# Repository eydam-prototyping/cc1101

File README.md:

# CC1101 Driver for Raspberry Pi and Micropython

This project provides a Python driver for the CC1101 transceiver chip, enabling seamless integration with Raspberry Pi and other compatible platforms. The driver supports data transmission and reception, making it ideal for wireless communication projects.

## Wiring

Connect two devices, if you want to run all samples. Otherwise you only need one.

| CC1101 (1) | CC1101 (2) | Raspberry Pi | Meaning      |
|------------|------------|--------------|--------------|
| VDD        | VDD        | 3.3V (17)    | Power Supply |
| GND        | GND        | GND (23)     | Ground       |
| MOSI       | MOSI       | GPIO10 (19)  | SPI MOSI     |
| MISO       | MISO       | GPIO9 (21)   | SPI MISO     |
| SCK        | SCK        | GPIO11 (23)  | SPI SCLK     |
| CSN        | -          | GPIO8 (24)   | SPI CE0      |
| -          | CSN        | GPIO7 (26)   | SPI CE1      |
| GDO0       | -          | GPIO23 (16)  | RX/TX Done   |
| -          | GDO0       | GPIO24 (18)  | RX/TX Done   |
| GDO2       | -          | GPIO17 (11)  | -            |
| -          | GDO2       | GPIO18 (12)  | -            |

## Usage
* Connect the CC1101 module to your hardware as per your wiring setup.

* Run an example script:

    * For transmission:
        ```bash
        python examples/transmitter.py
        ```
    * For reception:
        ```bash
        python examples/receiver.py
        ```

## Project Structure
* **src/:** Contains the main driver code.
* **examples/**: Example scripts for transmission and reception.
* **tests/**: Unit tests for the driver.

## Meaning of Parameters

### Base Frequency

```python
cc1101.configurator.set_base_frequency_hz(433.92e6)
cc1101.set_configuration()
```
The base frequency is a key parameter in configuring the CC1101 transceiver, as it defines the central frequency at which the device operates. This parameter determines the starting point of the RF (radio frequency) signal generation and reception, which is crucial for ensuring compatibility with the chosen communication standard or regulatory requirements.

The base frequency is typically set in the range of 300 MHz to 928 MHz, depending on the hardware and regional regulations. For example, in the ISM (Industrial, Scientific, and Medical) bands, common frequencies include 433 MHz, 868 MHz, and 915 MHz.

*Note: Make sure, you have the right Antenna connected*

### Modulation Format

```python
# 0: 2-FSK
# 1: GFSK
# 3: ASK_OOK
# 4: 4-FSK
# 7: MSK
cc1101.configurator.set_modulation_format(0)
cc1101.set_configuration()
```
The modulation format determines how data is encoded onto the carrier frequency for transmission and decoded during reception. This parameter is essential for ensuring compatibility between transmitting and receiving devices, as both must use the same modulation scheme to communicate effectively.

The CC1101 supports several modulation formats, including:
  * 2/4-FSK (Frequency Shift Keying): A robust modulation scheme commonly used in environments with high interference.
  * GFSK (Gaussian Frequency Shift Keying): A variation of FSK with smoother transitions, reducing spectral bandwidth and interference.
  * ASK/OOK (Amplitude Shift Keying/On-Off Keying): Simple schemes often used in low-power, short-range applications like remote controls.
  * MSK (Minimum Shift Keying): Provides high spectral efficiency, ideal for data-intensive applications.

The choice of modulation format impacts key aspects of the communication, including data rate, power consumption, and signal robustness. For example, FSK is highly reliable in noisy environments, while OOK is energy-efficient but more susceptible to interference.

#### 2-FSK (2 Frequency Shift Keying)

2-FSK is a digital modulation scheme where the carrier frequency shifts between two discrete frequencies to represent binary data (0 and 1). It is one of the simplest forms of frequency modulation and is widely used for robust communication in environments with noise or interference.

**Relevant CC1101 Parameters:**

  * Deviation: The difference between the carrier frequency and the modulated frequencies.

#### 4-FSK (4 Frequency Shift Keying)

Like 2-FSK, but with 4 Frequencies.

#### ASK (Amplitude Shift Keying) / OOK (On-Off Keying)

ASK (Amplitude Shift Keying) is a modulation scheme where the amplitude of the carrier signal varies to represent binary data. Unlike OOK, which is a subset of ASK with only two states (presence or absence of a signal), ASK can include more amplitude levels for more complex data encoding, though in most applications, it uses only two states:

High Amplitude represents binary 1.
Low Amplitude (or Zero in OOK) represents binary 0.
ASK/OOK is commonly used in simple, low-power communication systems such as wireless sensors, keyless entry systems, and remote controls.

**Relevant CC1101 Parameters:**

  * PA-Table Setting: \
      Byte 0 represents the power for a logical zero\
      Byte 1 represents the power for a logical one

  * FREND0.PA_POWER represents the PA power setting, that is used for a logical one. Default is 1.

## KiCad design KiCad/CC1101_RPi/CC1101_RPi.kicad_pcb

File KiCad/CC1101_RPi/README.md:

# PCB CC1101_RPi

## Wiring

| CH1, 433 MHz | CH2, 433 MHz | CH3, 868 MHz | CH4, 868 MHz | Raspberry Pi | Meaning      |
|--------------|--------------|--------------|--------------|--------------|--------------|
| VDD          | VDD          | -            | -            | 3.3V         | Power Supply |
| GND          | GND          | -            | -            | GND          | Ground       |
|              |              |              |              |              |              |
| MOSI         | MOSI         | -            | -            | GPIO10       | SPI0 MOSI    |
| MISO         | MISO         | -            | -            | GPIO9        | SPI0 MISO    |
| SCK          | SCK          | -            | -            | GPIO11       | SPI0 SCLK    |
|              |              |              |              |              |              |
| CSN          | -            | -            | -            | GPIO8        | SPI0 CE0     |
| GDO0         | -            | -            | -            | GPIO5        | -            |
| GDO2         | -            | -            | -            | GPIO6        | -            |
|              |              |              |              |              |              |
| -            | CSN          | -            | -            | GPIO7        | SPI0 CE1     |
| -            | GDO0         | -            | -            | GPIO22       | -            |
| -            | GDO2         | -            | -            | GPIO23       | -            |
|              |              |              |              |              |              |
| -            | -            | MOSI         | MOSI         | GPIO20       | SPI1 MOSI    |
| -            | -            | MISO         | MISO         | GPIO19       | SPI1 MISO    |
| -            | -            | SCK          | SCK          | GPIO21       | SPI1 SCLK    |
|              |              |              |              |              |              |
| -            | -            | CSN          | -            | GPIO18       | SPI1 CE0     |
| -            | -            | GDO0         | -            | GPIO24       | -            |
| -            | -            | GDO2         | -            | GPIO25       | -            |
|              |              |              |              |              |              |
| -            | -            | -            | CSN          | GPIO17       | SPI1 CE1     |
| -            | -            | -            | GDO0         | GPIO26       | -            |
| -            | -            | -            | GDO2         | GPIO27       | -            |

# Setup

Enable I2C and SPI in `/boot/firmware/config.txt`:

```
dtparam=i2c_arm=on
dtparam=spi=on
dtoverlay=spi1-2cs
```

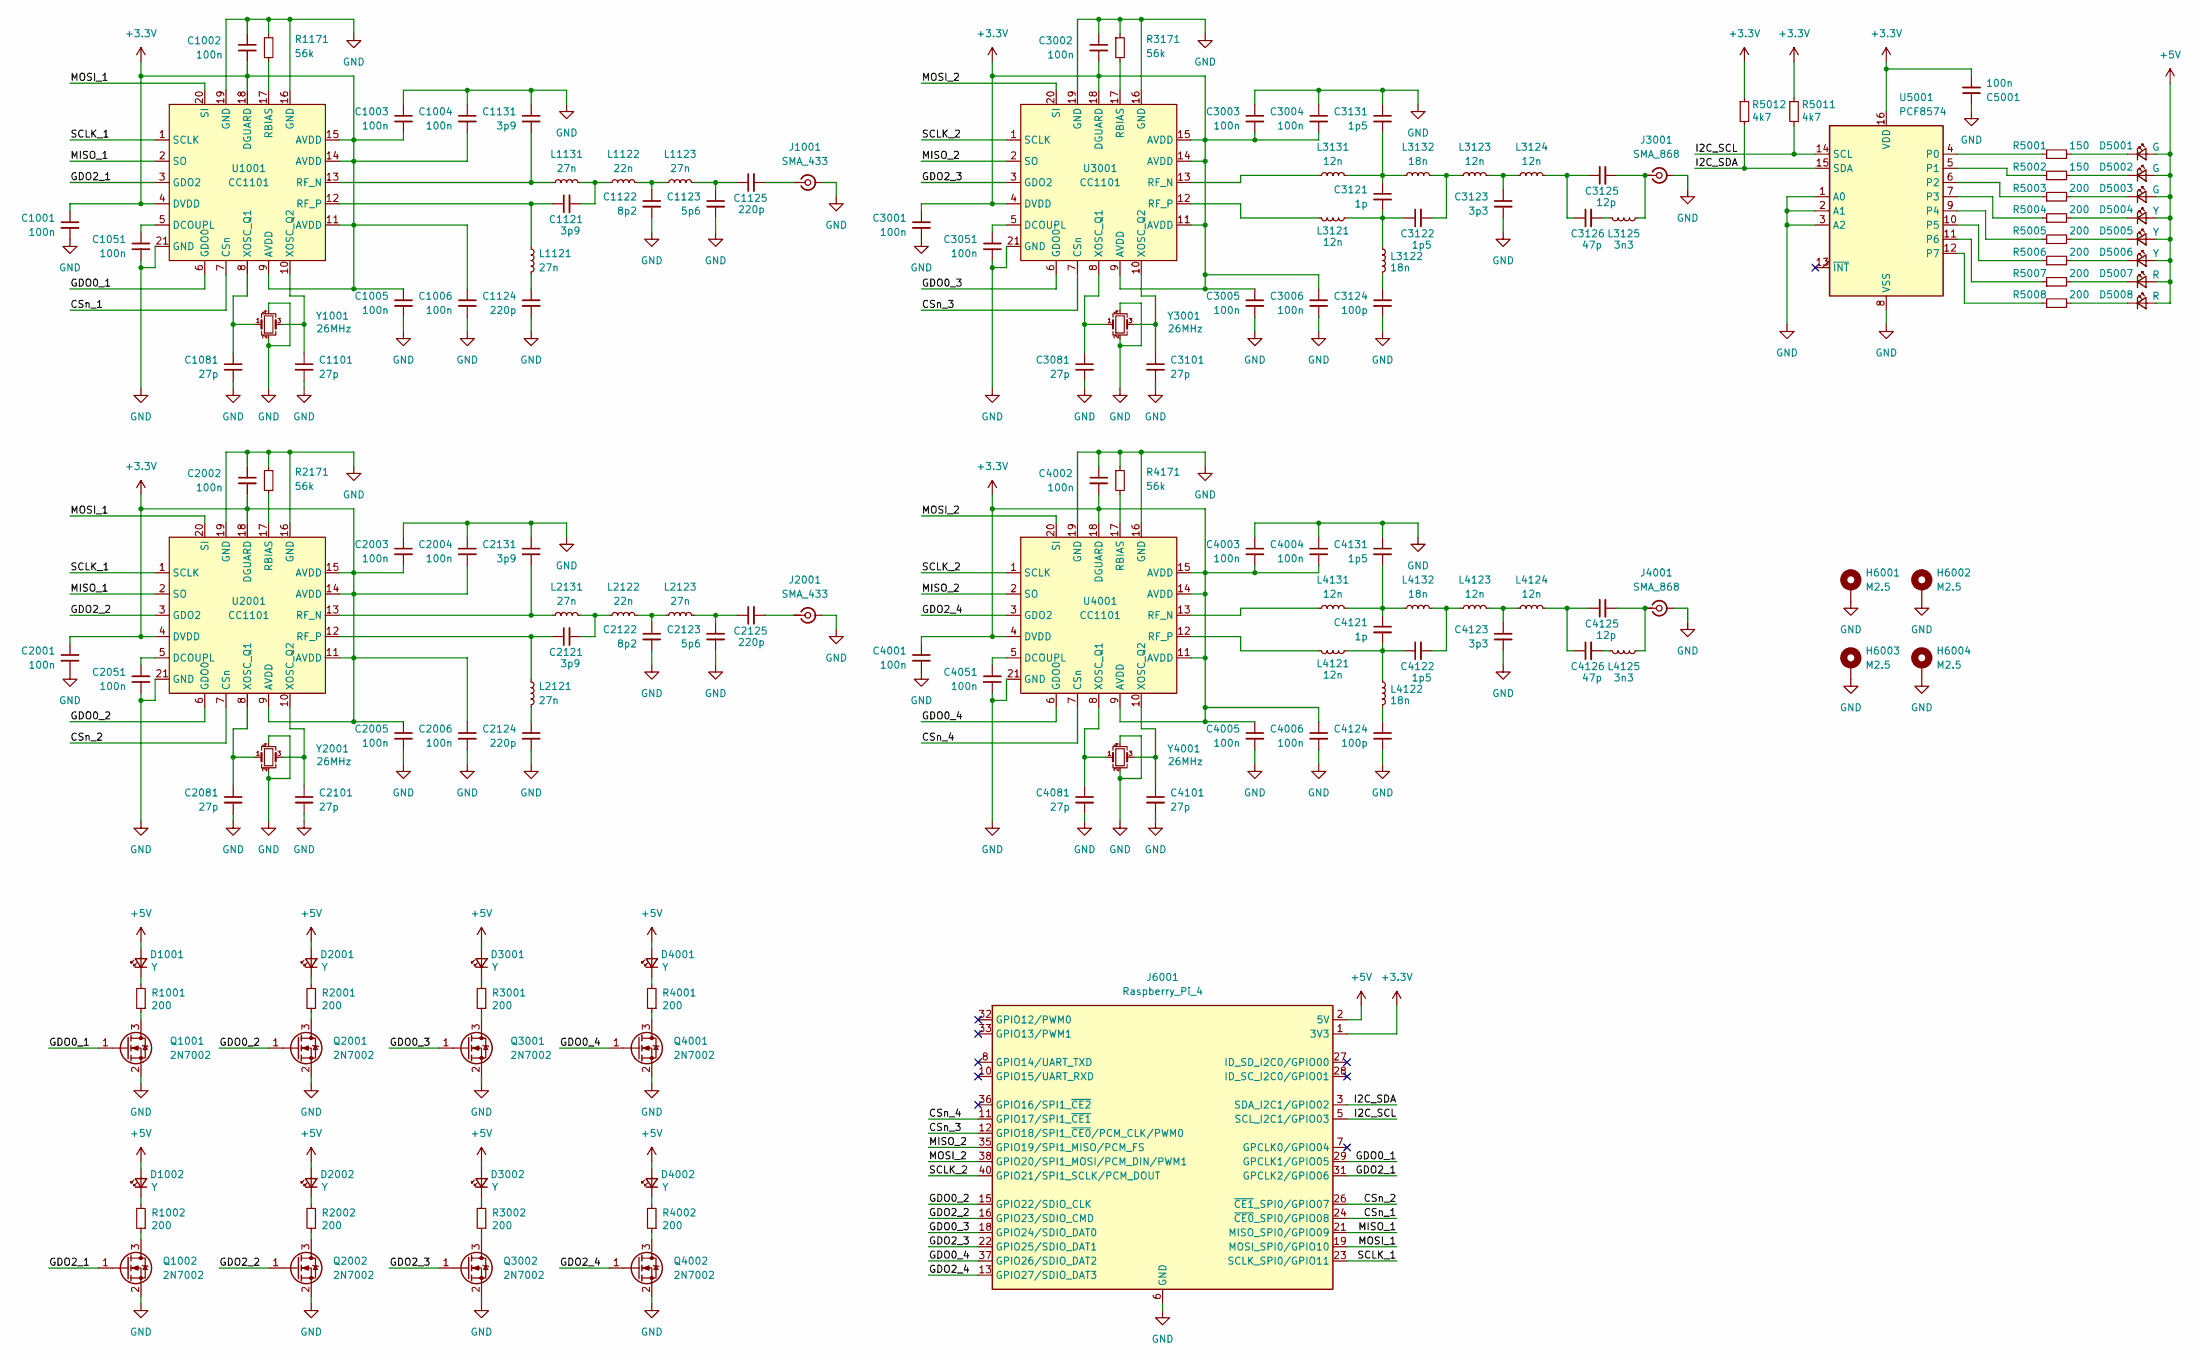
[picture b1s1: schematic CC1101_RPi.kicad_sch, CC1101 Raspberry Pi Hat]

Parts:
C1001, C1002, C1003, C1004, C1005, C1006, C1051, C2001, C2002, C2003, C2004, C2005, C2006, C2051, C3001, C3002, C3003, C3004, C3005, C3006, C3051, C4001, C4002, C4003, C4004, C4005, C4006, C4051, C5001: 100n; C_0402_1005Metric; MFRPartNo CL05B104KB54PNC; LCSC C307331
C1081, C1101, C2081, C2101, C3081, C3101, C4081, C4101: 27p; C_0402_1005Metric; MFRPartNo GRM1555C1H270FA01D; LCSC C161544
C1121, C1131, C2121, C2131: 3p9; C_0402_1005Metric; MFRPartNo GRM1555C1H3R9CA01D; LCSC C85940
C1122, C2122: 8p2; C_0402_1005Metric; MFRPartNo GRM1555C1H8R2CA01D; LCSC C76984
C1123, C2123: 5p6; C_0402_1005Metric; MFRPartNo GRM1555C1H5R6BA01D; LCSC C76976
C1124, C1125, C2124, C2125: 220p; C_0402_1005Metric; MFRPartNo GRM1555C1H221JA01D; LCSC C71693
C3121, C4121: 1p; C_0402_1005Metric; MFRPartNo GRM1555C1H1R0CA01D; LCSC C76953
C3122, C3131, C4122, C4131: 1p5; C_0402_1005Metric; MFRPartNo GRM1555C1H1R5CA01D; LCSC C76958
C3123, C4123: 3p3; C_0402_1005Metric; MFRPartNo GRM1555C1H3R3CA01D; LCSC C76968
C3124, C4124: 100p; C_0402_1005Metric; MFRPartNo GRM1555C1H101JA01D; LCSC C77177
C3125, C4125: 12p; C_0402_1005Metric; MFRPartNo GRM1555C1H120JA01D; LCSC C76948
C3126, C4126: 47p; C_0402_1005Metric; MFRPartNo GRM1555C1H470JA01D; LCSC C76970
D1001, D1002, D2001, D2002, D3001, D3002, D4001, D4002, D5004, D5005, D5006: Y; LED_0805_2012Metric; MFRPartNo KT-0805Y; LCSC C2296
D5001, D5002, D5003: G; LED_0805_2012Metric; MFRPartNo KT-0805G; LCSC C2297
D5007, D5008: R; LED_0805_2012Metric; MFRPartNo KT-0805R; LCSC C2295
H6001, H6002, H6003, H6004: M2.5; MountingHole_2.7mm_M2.5_DIN965_Pad
J1001, J2001: SMA_433; SMA_BAT_Wireless_BWSMA-KWE-Z001; MFRPartNo BWSMA-KE-Z001; LCSC C496549
J3001, J4001: SMA_868; SMA_BAT_Wireless_BWSMA-KWE-Z001; MFRPartNo BWSMA-KE-Z001; LCSC C496549
J6001: Raspberry_Pi_4; PinHeader_2x20_P2.54mm_Vertical
L1121, L1123, L1131, L2121, L2123, L2131: 27n; L_0402_1005Metric; MFRPartNo LQG15HS27NJ02D; LCSC C12669
L1122, L2122: 22n; L_0402_1005Metric; MFRPartNo LQG15HS22NJ02D; LCSC C12670
L3121, L3123, L3124, L3131, L4121, L4123, L4124, L4131: 12n; L_0402_1005Metric; MFRPartNo LQW15AN12NG80D; LCSC C3223181
L3122, L3132, L4122, L4132: 18n; L_0402_1005Metric; MFRPartNo LQW15AN18NG00D; LCSC C91622
L3125, L4125: 3n3; L_0402_1005Metric; MFRPartNo LQW15AN3N3C80D; LCSC C237574
Q1001, Q1002, Q2001, Q2002, Q3001, Q3002, Q4001, Q4002: 2N7002; SOT-23; MFRPartNo 2N7002; LCSC C8545
R1001, R1002, R2001, R2002, R3001, R3002, R4001, R4002, R5003, R5004, R5005, R5006, R5007, R5008: 200; R_0603_1608Metric; MFRPartNo 0603WAF2000T5E; LCSC C8218
R1171, R2171, R3171, R4171: 56k; R_0603_1608Metric; MFRPartNo 0603WAF5602T5E; LCSC C23206
R5001, R5002: 150; R_0603_1608Metric; MFRPartNo 0603WAF1500T5E; LCSC C22808
R5011, R5012: 4k7; R_0603_1608Metric; MFRPartNo 0603WAF4701T5E; LCSC C23162
U1001, U2001, U3001, U4001: CC1101; Texas_RGP0020D_VQFN-20-1EP_4x4mm_P0.5mm_EP2.7x2.7mm_Thermal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; MFRPartNo CC1101RGPR; LCSC C29953
U5001: PCF8574; SOIC-16W_7.5x10.3mm_P1.27mm; MFRPartNo PCF8574T/3,518; LCSC C7605
Y1001, Y2001, Y3001, Y4001: 26MHz; Crystal_SMD_3225-4Pin_3.2x2.5mm; MFRPartNo NX3225GA-26MHZ-EXS00A-CG01972; LCSC C485372

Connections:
+3.3V: C1001.1, C1002.2, C1003.2, C1004.2, C1005.1, C1006.1, C2001.1, C2002.2, C2003.2, C2004.2, C2005.1, C2006.1, C3001.1, C3002.2, C3003.2, C3004.2, C3005.1, C3006.1, C4001.1, C4002.2, C4003.2, C4004.2, C4005.1, C4006.1, C5001.2, J6001.1 (3V3), J6001.17 (3V3), R5011.1, R5012.1, U1001.4 (DVDD), U1001.9 (AVDD), U1001.11 (AVDD), U1001.14 (AVDD), U1001.15 (AVDD), U1001.18 (DGUARD), U2001.4 (DVDD), U2001.9 (AVDD), U2001.11 (AVDD), U2001.14 (AVDD), U2001.15 (AVDD), U2001.18 (DGUARD), U3001.4 (DVDD), U3001.9 (AVDD), U3001.11 (AVDD), U3001.14 (AVDD), U3001.15 (AVDD), U3001.18 (DGUARD), U4001.4 (DVDD), U4001.9 (AVDD), U4001.11 (AVDD), U4001.14 (AVDD), U4001.15 (AVDD), U4001.18 (DGUARD), U5001.16 (VDD)
+5V: D1001.2 (A), D1002.2 (A), D2001.2 (A), D2002.2 (A), D3001.2 (A), D3002.2 (A), D4001.2 (A), D4002.2 (A), D5001.2 (A), D5002.2 (A), D5003.2 (A), D5004.2 (A), D5005.2 (A), D5006.2 (A), D5007.2 (A), D5008.2 (A), J6001.2 (5V), J6001.4 (5V)
/CSn_1: J6001.24 (~CE0_SPI0/GPIO08), U1001.7 (CSn)
/CSn_2: J6001.26 (~CE1_SPI0/GPIO07), U2001.7 (CSn)
/CSn_3: J6001.12 (GPIO18/SPI1_~CE0/PCM_CLK/PWM0), U3001.7 (CSn)
/CSn_4: J6001.11 (GPIO17/SPI1_~CE1), U4001.7 (CSn)
/GDO0_1: J6001.29 (GPCLK1/GPIO05), Q1001.1 (G), U1001.6 (GDO0)
/GDO0_2: J6001.15 (GPIO22/SDIO_CLK), Q2001.1 (G), U2001.6 (GDO0)
/GDO0_3: J6001.18 (GPIO24/SDIO_DAT0), Q3001.1 (G), U3001.6 (GDO0)
/GDO0_4: J6001.37 (GPIO26/SDIO_DAT2), Q4001.1 (G), U4001.6 (GDO0)
/GDO2_1: J6001.31 (GPCLK2/GPIO06), Q1002.1 (G), U1001.3 (GDO2)
/GDO2_2: J6001.16 (GPIO23/SDIO_CMD), Q2002.1 (G), U2001.3 (GDO2)
/GDO2_3: J6001.22 (GPIO25/SDIO_DAT1), Q3002.1 (G), U3001.3 (GDO2)
/GDO2_4: J6001.13 (GPIO27/SDIO_DAT3), Q4002.1 (G), U4001.3 (GDO2)
/I2C_SCL: J6001.5 (SCL_I2C1/GPIO03), R5011.2, U5001.14 (SCL)
/I2C_SDA: J6001.3 (SDA_I2C1/GPIO02), R5012.2, U5001.15 (SDA)
/MISO_1: J6001.21 (MISO_SPI0/GPIO09), U1001.2 (SO), U2001.2 (SO)
/MISO_2: J6001.35 (GPIO19/SPI1_MISO/PCM_FS), U3001.2 (SO), U4001.2 (SO)
/MOSI_1: J6001.19 (MOSI_SPI0/GPIO10), U1001.20 (SI), U2001.20 (SI)
/MOSI_2: J6001.38 (GPIO20/SPI1_MOSI/PCM_DIN/PWM1), U3001.20 (SI), U4001.20 (SI)
/SCLK_1: J6001.23 (SCLK_SPI0/GPIO11), U1001.1 (SCLK), U2001.1 (SCLK)
/SCLK_2: J6001.40 (GPIO21/SPI1_SCLK/PCM_DOUT), U3001.1 (SCLK), U4001.1 (SCLK)
GND: C1001.2, C1002.1, C1003.1, C1004.1, C1005.2, C1006.2, C1051.2, C1081.2, C1101.2, C1122.2, C1123.2, C1124.2, C1131.1, C2001.2, C2002.1, C2003.1, C2004.1, C2005.2, C2006.2, C2051.2, C2081.2, C2101.2, C2122.2, C2123.2, C2124.2, C2131.1, C3001.2, C3002.1, C3003.1, C3004.1, C3005.2, C3006.2, C3051.2, C3081.2, C3101.2, C3123.2, C3124.2, C3131.1, C4001.2, C4002.1, C4003.1, C4004.1, C4005.2, C4006.2, C4051.2, C4081.2, C4101.2, C4123.2, C4124.2, C4131.1, C5001.1, H6001.1, H6002.1, H6003.1, H6004.1, J1001.2 (Ext), J2001.2 (Ext), J3001.2 (Ext), J4001.2 (Ext), J6001.6 (GND), J6001.9 (GND), J6001.14 (GND), J6001.20 (GND), J6001.25 (GND), J6001.30 (GND), J6001.34 (GND), J6001.39 (GND), Q1001.2 (S), Q1002.2 (S), Q2001.2 (S), Q2002.2 (S), Q3001.2 (S), Q3002.2 (S), Q4001.2 (S), Q4002.2 (S), R1171.1, R2171.1, R3171.1, R4171.1, U1001.16 (GND), U1001.19 (GND), U1001.21 (GND), U2001.16 (GND), U2001.19 (GND), U2001.21 (GND), U3001.16 (GND), U3001.19 (GND), U3001.21 (GND), U4001.16 (GND), U4001.19 (GND), U4001.21 (GND), U5001.1 (A0), U5001.2 (A1), U5001.3 (A2), U5001.8 (VSS), Y1001.2, Y1001.4, Y2001.2, Y2001.4, Y3001.2, Y3001.4, Y4001.2, Y4001.4; also elsewhere on the board
unnamed: C1121.2, L1122.1, L1131.2
unnamed: C1122.1, L1122.2, L1123.1
unnamed: C1123.1, C1125.1, L1123.2
unnamed: C1124.1, L1121.2
unnamed: C2121.2, L2122.1, L2131.2
unnamed: C2122.1, L2122.2, L2123.1
unnamed: C2123.1, C2125.1, L2123.2
unnamed: C2124.1, L2121.2
unnamed: C3121.1, C3131.2, L3131.2, L3132.1
unnamed: C3121.2, C3122.1, L3121.2, L3122.1
unnamed: C3122.2, L3123.1, L3132.2
unnamed: C3123.1, L3123.2, L3124.1
unnamed: C3124.1, L3122.2
unnamed: C3125.1, C3126.1, L3124.2
unnamed: C3126.2, L3125.1
unnamed: C4121.1, C4131.2, L4131.2, L4132.1
unnamed: C4121.2, C4122.1, L4121.2, L4122.1
unnamed: C4122.2, L4123.1, L4132.2
unnamed: C4123.1, L4123.2, L4124.1
unnamed: C4124.1, L4122.2
unnamed: C4125.1, C4126.1, L4124.2
unnamed: C4126.2, L4125.1
unnamed: D1001.1 (K), R1001.2
unnamed: D1002.1 (K), R1002.2
unnamed: D2001.1 (K), R2001.2
unnamed: D2002.1 (K), R2002.2
unnamed: D3001.1 (K), R3001.2
unnamed: D3002.1 (K), R3002.2
unnamed: D4001.1 (K), R4001.2
unnamed: D4002.1 (K), R4002.2
unnamed: D5001.1 (K), R5001.2
unnamed: D5002.1 (K), R5002.2
unnamed: D5003.1 (K), R5003.2
unnamed: D5004.1 (K), R5004.2
unnamed: D5005.1 (K), R5005.2
unnamed: D5006.1 (K), R5006.2
unnamed: D5007.1 (K), R5007.2
unnamed: D5008.1 (K), R5008.2
unnamed: C1125.2, J1001.1 (In)
unnamed: C2125.2, J2001.1 (In)
unnamed: C3125.2, J3001.1 (In), L3125.2
unnamed: C4125.2, J4001.1 (In), L4125.2
unnamed: Q1001.3 (D), R1001.1
unnamed: Q1002.3 (D), R1002.1
unnamed: Q2001.3 (D), R2001.1
unnamed: Q2002.3 (D), R2002.1
unnamed: Q3001.3 (D), R3001.1
unnamed: Q3002.3 (D), R3002.1
unnamed: Q4001.3 (D), R4001.1
unnamed: Q4002.3 (D), R4002.1
unnamed: C1051.1, U1001.5 (DCOUPL)
unnamed: R1171.2, U1001.17 (RBIAS)
unnamed: C1131.2, L1131.1, U1001.13 (RF_N)
unnamed: C1121.1, L1121.1, U1001.12 (RF_P)
unnamed: C1081.1, U1001.8 (XOSC_Q1), Y1001.1
unnamed: C1101.1, U1001.10 (XOSC_Q2), Y1001.3
unnamed: C2051.1, U2001.5 (DCOUPL)
unnamed: R2171.2, U2001.17 (RBIAS)
unnamed: C2131.2, L2131.1, U2001.13 (RF_N)
unnamed: C2121.1, L2121.1, U2001.12 (RF_P)
unnamed: C2081.1, U2001.8 (XOSC_Q1), Y2001.1
unnamed: C2101.1, U2001.10 (XOSC_Q2), Y2001.3
unnamed: C3051.1, U3001.5 (DCOUPL)
unnamed: R3171.2, U3001.17 (RBIAS)
unnamed: L3131.1, U3001.13 (RF_N)
unnamed: L3121.1, U3001.12 (RF_P)
unnamed: C3081.1, U3001.8 (XOSC_Q1), Y3001.1
unnamed: C3101.1, U3001.10 (XOSC_Q2), Y3001.3
unnamed: C4051.1, U4001.5 (DCOUPL)
unnamed: R4171.2, U4001.17 (RBIAS)
unnamed: L4131.1, U4001.13 (RF_N)
unnamed: L4121.1, U4001.12 (RF_P)
unnamed: C4081.1, U4001.8 (XOSC_Q1), Y4001.1
unnamed: C4101.1, U4001.10 (XOSC_Q2), Y4001.3
unnamed: R5001.1, U5001.4 (P0)
unnamed: R5002.1, U5001.5 (P1)
unnamed: R5003.1, U5001.6 (P2)
unnamed: R5004.1, U5001.7 (P3)
unnamed: R5005.1, U5001.9 (P4)
unnamed: R5006.1, U5001.10 (P5)
unnamed: R5007.1, U5001.11 (P6)
unnamed: R5008.1, U5001.12 (P7)

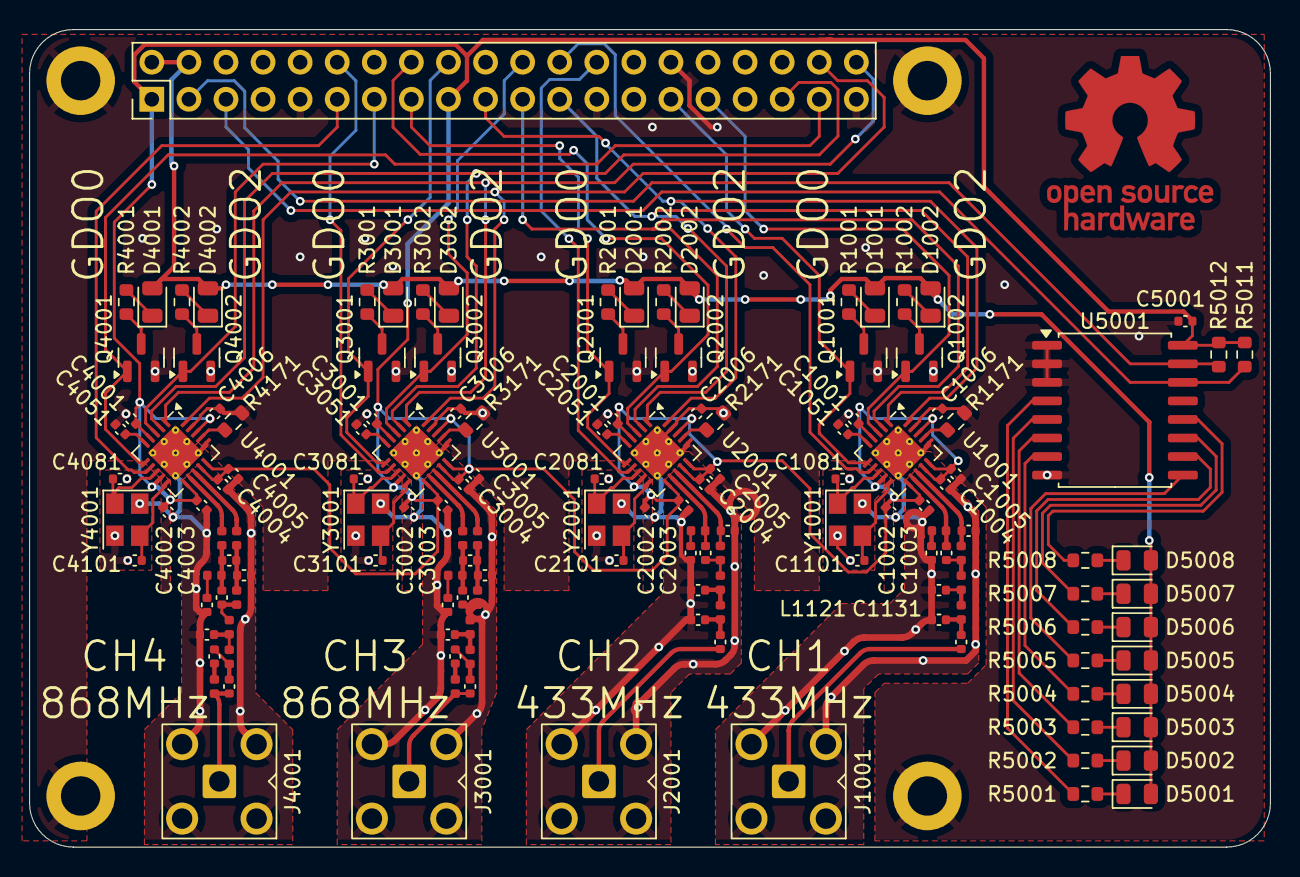
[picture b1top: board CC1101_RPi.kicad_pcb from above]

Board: 2 copper layers, 85.0 x 56.0 mm, 149 parts (0 on the bottom side), 105 nets.

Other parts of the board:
H1, H2, H3: M2.5; MountingHole_2.7mm_M2.5_DIN965_Pad

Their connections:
GND: H1.1, H2.1, H3.1; also elsewhere on the board

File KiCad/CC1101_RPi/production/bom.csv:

Designator,Footprint,Quantity,Value,LCSC Part #
"C1001, C1002, C1003, C1004, C1005, C1006, C1051, C2001, C2002, C2003, C2004, C2005, C2006, C2051, C3001, C3002, C3003, C3004, C3005, C3006, C3051, C4001, C4002, C4003, C4004, C4005, C4006, C4051, C5001",0402,29,100n,C307331
"C1081, C1101, C2081, C2101, C3081, C3101, C4081, C4101",0402,8,27p,C161544
"C1121, C1131, C2121, C2131",0402,4,3p9,C85940
"C1122, C2122",0402,2,8p2,C76984
"C1123, C2123",0402,2,5p6,C76976
"C1124, C1125, C2124, C2125",0402,4,220p,C71693
"C3121, C4121",0402,2,1p,C76953
"C3122, C3131, C4122, C4131",0402,4,1p5,C76958
"C3123, C4123",0402,2,3p3,C76968
"C3124, C4124",0402,2,100p,C77177
"C3125, C4125",0402,2,12p,C76948
"C3126, C4126",0402,2,47p,C76970
"D1001, D1002, D2001, D2002, D3001, D3002, D4001, D4002, D5004, D5005, D5006",0805,11,Y,C2296
"D5001, D5002, D5003",0805,3,G,C2297
"D5007, D5008",0805,2,R,C2295
"J1001, J2001",SMA_BAT_Wireless_BWSMA-KWE-Z001,2,SMA_433,C496549
"J3001, J4001",SMA_BAT_Wireless_BWSMA-KWE-Z001,2,SMA_868,C496549
J6001,PinHeader_2x20_P2.54mm_Vertical,1,Raspberry_Pi_4,
"L1121, L1123, L1131, L2121, L2123, L2131",0402,6,27n,C12669
"L1122, L2122",0402,2,22n,C12670
"L3121, L3123, L3124, L3131, L4121, L4123, L4124, L4131",0402,8,12n,C3223181
"L3122, L3132, L4122, L4132",0402,4,18n,C91622
"L3125, L4125",0402,2,3n3,C237574
"Q1001, Q1002, Q2001, Q2002, Q3001, Q3002, Q4001, Q4002",SOT-23,8,2N7002,C8545
"R1001, R1002, R2001, R2002, R3001, R3002, R4001, R4002, R5003, R5004, R5005, R5006, R5007, R5008",0603,14,200,C8218
"R1171, R2171, R3171, R4171",0603,4,56k,C23206
"R5001, R5002",0603,2,150,C22808
"R5011, R5012",0603,2,4k7,C23162
"U1001, U2001, U3001, U4001",Texas_RGP0020D_VQFN-20-1EP_4x4mm_P0.5mm_EP2.7x2.7mm_ThermalVias,4,CC1101,C29953
U5001,SOIC-16W_7.5x10.3mm_P1.27mm,1,PCF8574,C7605
"Y1001, Y2001, Y3001, Y4001",Crystal_SMD_3225-4Pin_3.2x2.5mm,4,26MHz,C485372

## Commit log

2024-12-03 Readme added
2024-12-03 load presets function added
2024-12-03 kia settings, samples
2024-12-07 Preset added
2024-12-07 Receiving/Transmitting improved
2024-12-07 Preset renamed
2024-12-07 replaced print with log statements
2024-12-07 documentation
2024-12-07 preset loading
2024-12-07 bug in modulation format fixed
2024-12-07 documentation for ask ook added
2024-12-07 set FREND0 register to 1 when using ASK/OOK
2024-12-07 ASK OOK image
2024-12-08 Received Packet Length fixed
2024-12-14 RSSI reading
2024-12-14 rssi_monitor
2024-12-14 packet logger
2024-12-14 license
2024-12-14 Update issue templates
2024-12-14 package created
2024-12-14 pyproject.toml
2024-12-14 tests fixed
2024-12-15 folder name changed
2024-12-15 channel spacing and number
2024-12-15 example for multi channel transmitter
2024-12-25 refactoring
2024-12-25 Refactoring, AGC
2024-12-26 Imports, Stubs
2024-12-26 Stub added
2024-12-26 assertions
2024-12-30 Production to JLCPCB
2025-01-02 Rust module added
2025-01-02 files moved
2025-01-02 workflow for both packets
2025-01-02 workflow
2025-01-11 first example for pcb
2025-01-11 multiple changes
2025-01-11 config for analog discovery oscilloscope
2025-01-11 imports for testing
2025-01-11 path
2025-01-11 tests
2025-01-11 tests added
2025-01-12 fixes for pcb
2025-02-09 princeton24bit
2025-02-14 changes for sync serial transmit
2025-02-15 Packet ausgelagert
2025-02-15 gdo config moved to packet mode
2025-02-15 packet based tx and rx
2025-02-18 pt2262
2025-02-18 Testresults
2025-02-19 restructuring
2025-02-19 modulation
2025-02-20 modulation ask/ook
